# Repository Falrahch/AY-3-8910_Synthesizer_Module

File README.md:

# AY-3-8910_Synthesizer_Module

This respository contains all sources needed to create a synthesizer module based on the AY-3-8910 audio chip from General Instruments. The module is based on a ARM Cortex M3: the STM32F103CBT6.
The module is interfaced by a MIDI controller keyboard over a MIDI interface. The output of the module should be fed into an amplifier and can then be played on a speaker.

## Flashing the Module
The PCB has a SWD interface on the three pins on one side of the microcontroller. The controller can be flashed using and ST-Link V2 flasher and OpenOCD (version 0.10.0-13 should work just fine). The configuration-file in "tools" can be used to do so. The name of the binary has to be changed in the file from "AY-3-8910.bin" to the name of the binary that should be flashed. The binary has to be in the same direction as the config-file (OpenOCD/0.10.0-13/scripts). The flashing process is started via a terminal like powershell:

`openocd -f interface/stlink.cfg -f target/stm32f1x.cfg -f flash_stm32f1x.cfg`

It is possible that the flashing won't work the first time and has to be started a second time.

## Adjusting the Clock Frequency
The clock frequency that is sent to the audio chip can be changed in the source code. This will change the tone range of the chip. With a higher clock frequency the range of playable frequencies will shift up. Also, the resolution between the frequencies will get higher.

Acoording to the manufacturer frequencies between 1 MHz and 2 MHz can be used for the chip. However, up to 8 MHz was tested and works fine without audio distortions.

The frequency for the clock is set in *main.cpp* in the function *setupTimer()*. The register values of Timer 3 have to be set by calculating with the CPU frequncy. Since the CPU frequency is 64 MHz and the clock frequency is set to 2 MHz, the auto-reload value is set to 32. To get different frequencies this register and, if necessary, the prescaler register have to be set. The reference manual and tutorials should be consulted if necessary.

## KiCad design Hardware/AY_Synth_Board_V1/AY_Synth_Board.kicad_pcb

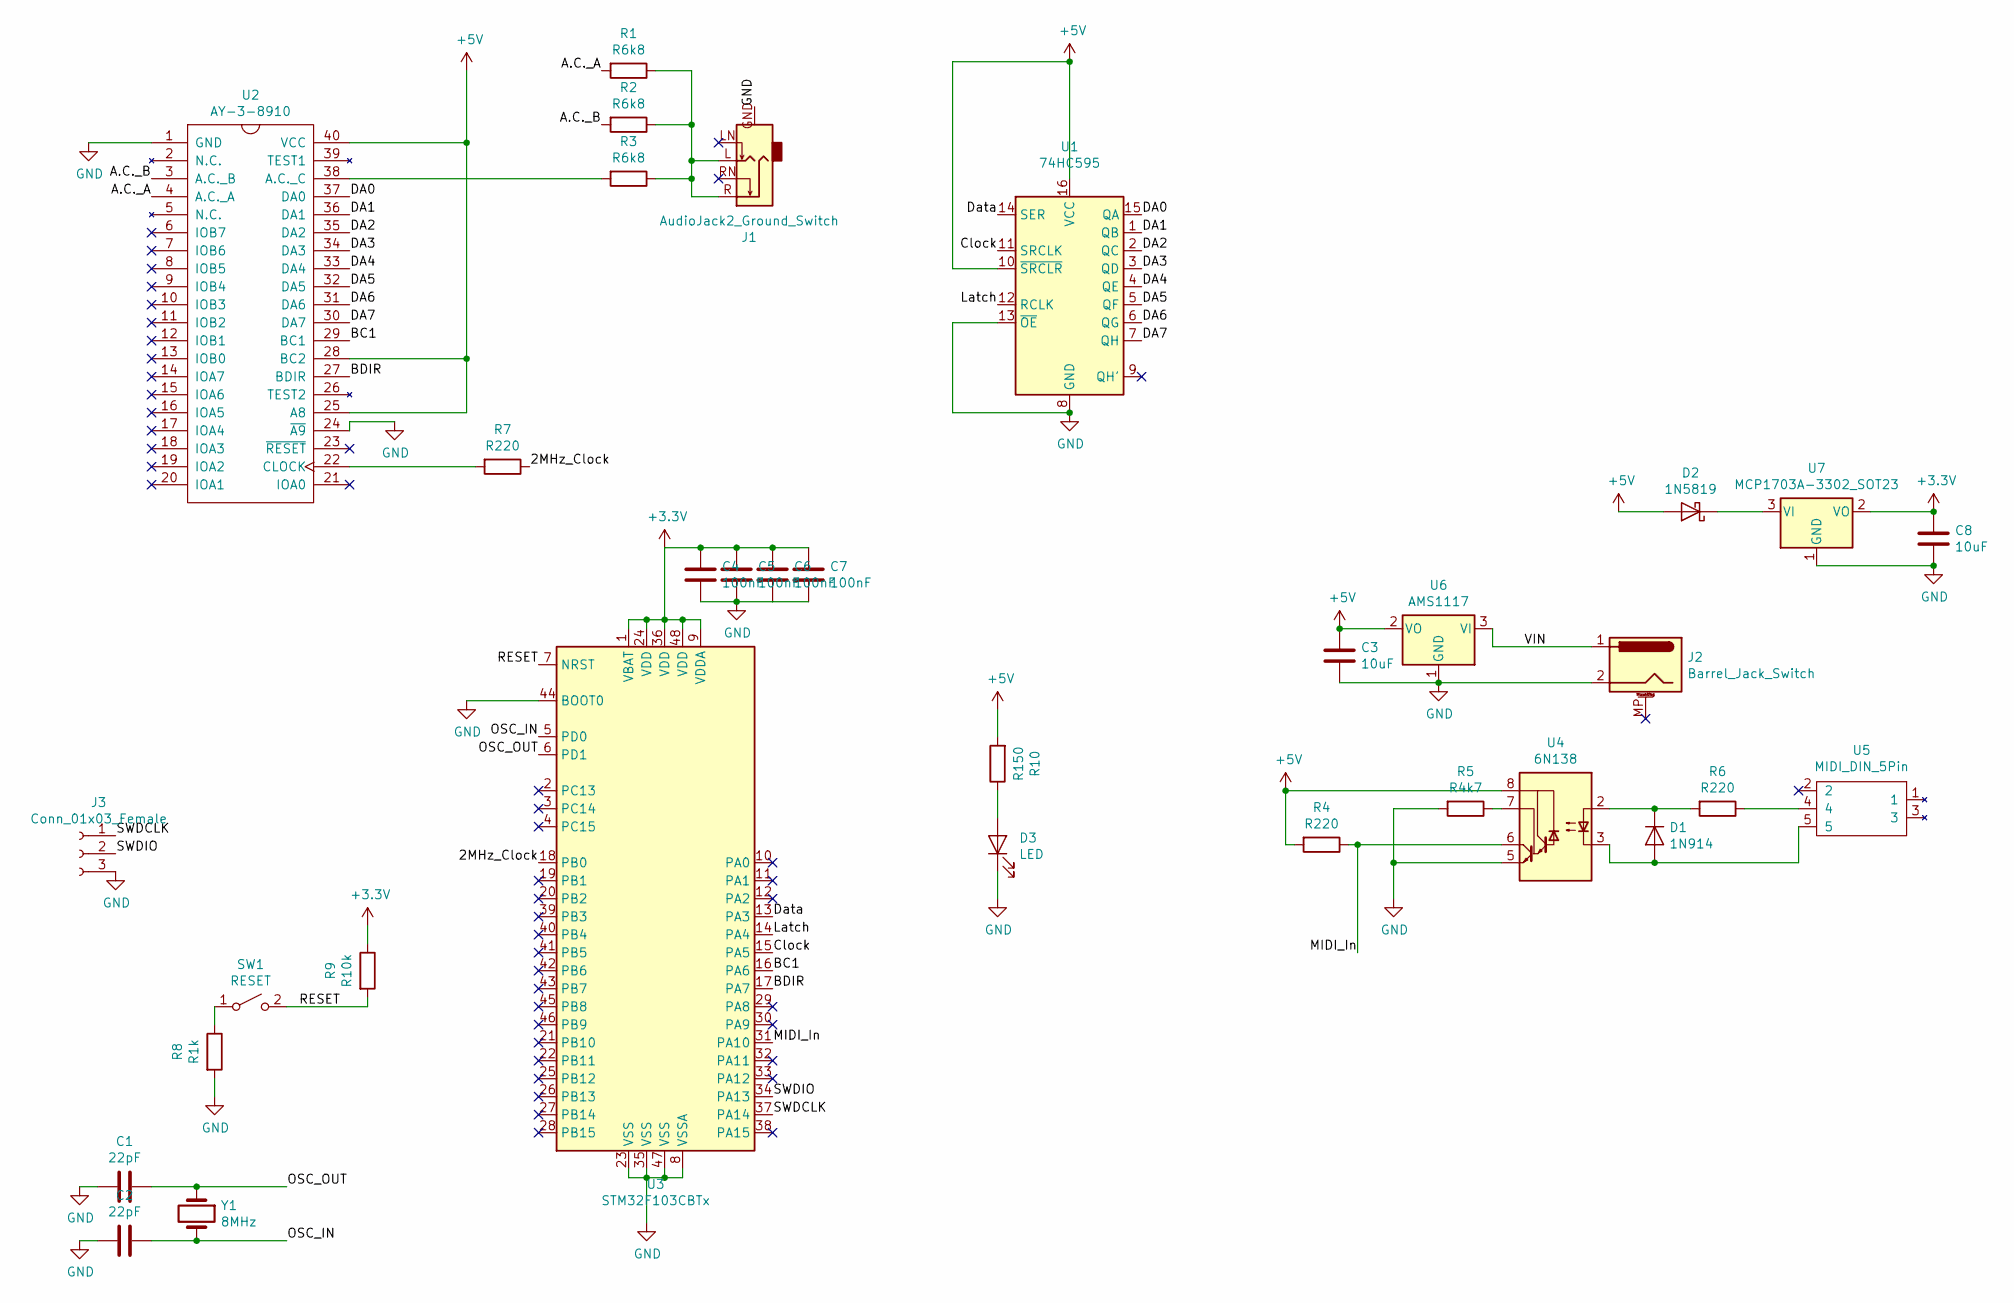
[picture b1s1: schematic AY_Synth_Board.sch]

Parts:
C1, C2: 22pF; C_1206_3216Metric_Pad1.42x1.75mm_HandSolder
C3, C8: 10uF; C_1206_3216Metric_Pad1.42x1.75mm_HandSolder
C4, C5, C6, C7: 100nF; C_1206_3216Metric_Pad1.42x1.75mm_HandSolder
D1: 1N914; D_1206_3216Metric_Pad1.42x1.75mm_HandSolder
D2: 1N5819; D_SOD-123
D3: LED; LED_1206_3216Metric_Pad1.42x1.75mm_HandSolder
J1: AudioJack2_Ground_Switch; Jack_3.5mm_Ledino_KB3SPRS_Horizontal_Custom
J2: Barrel_Jack_Switch; BarrelJack_Horizontal_MP
J3: Conn_01x03_Female; PinHeader_1x03_P2.54mm_Vertical
R1, R2, R3: R6k8; R_1206_3216Metric_Pad1.42x1.75mm_HandSolder
R4, R6, R7: R220; R_1206_3216Metric_Pad1.42x1.75mm_HandSolder
R5: R4k7; R_1206_3216Metric_Pad1.42x1.75mm_HandSolder
R8: R1k; R_1206_3216Metric_Pad1.42x1.75mm_HandSolder
R9: R10k; R_1206_3216Metric_Pad1.42x1.75mm_HandSolder
R10: R150; R_1206_3216Metric_Pad1.42x1.75mm_HandSolder
SW1: RESET; SW_SPST_TL3305A
U1: 74HC595; DIP-16_W7.62mm_Socket
U2: AY-3-8910; DIP-40_W15.24mm_Socket
U3: STM32F103CBTx; LQFP-48_7x7mm_P0.5mm
U4: 6N138; DIP-8_W7.62mm_Socket
U5: MIDI_DIN_5Pin; din_5_econet_pcb_mount
U6: AMS1117; SOT-223
U7: MCP1703A-3302_SOT23; SOT-23
Y1: 8MHz; Crystal_HC18-U_Vertical

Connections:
+3V3: C4.1, C5.1, C6.1, C7.1, C8.1, R9.1, U3.1 (VBAT), U3.9 (VDDA), U3.24 (VDD), U3.36 (VDD), U3.48 (VDD), U7.2 (VO)
+5V: C3.1, D2.2 (A), R4.2, R10.2, U1.10 (~SRCLR), U1.16 (VCC), U2.25 (A8), U2.28 (BC2), U2.40 (VCC), U4.8 (VCC), U6.2 (VO)
/2MHz_Clock: R7.1, U3.18 (PB0)
/A.C._A: R1.2, U2.4 (A.C._A)
/A.C._B: R2.2, U2.3 (A.C._B)
/BC1: U2.29 (BC1), U3.16 (PA6)
/BDIR: U2.27 (BDIR), U3.17 (PA7)
/Clock: U1.11 (SRCLK), U3.15 (PA5)
/DA0: U1.15 (QA), U2.37 (DA0)
/DA1: U1.1 (QB), U2.36 (DA1)
/DA2: U1.2 (QC), U2.35 (DA2)
/DA3: U1.3 (QD), U2.34 (DA3)
/DA4: U1.4 (QE), U2.33 (DA4)
/DA5: U1.5 (QF), U2.32 (DA5)
/DA6: U1.6 (QG), U2.31 (DA6)
/DA7: U1.7 (QH), U2.30 (DA7)
/Data: U1.14 (SER), U3.13 (PA3)
/Latch: U1.12 (RCLK), U3.14 (PA4)
/MIDI_In: R4.1, U3.31 (PA10), U4.6 (VO2)
/OSC_IN: C2.1, U3.5 (PD0), Y1.2
/OSC_OUT: C1.1, U3.6 (PD1), Y1.1
/RESET: R9.2, SW1.2 (B), U3.7 (NRST)
/SWDCLK: J3.1, U3.37 (PA14)
/SWDIO: J3.2, U3.34 (PA13)
/VIN: J2.1, U6.3 (VI)
GND: C1.2, C2.2, C3.2, C4.2, C5.2, C6.2, C7.2, C8.2, D3.1 (K), J1.GND, J2.2, J3.3, R5.2, R8.2, U1.8 (GND), U1.13 (~OE), U2.1 (GND), U2.24 (~A9), U3.8 (VSSA), U3.23 (VSS), U3.35 (VSS), U3.44 (BOOT0), U3.47 (VSS), U4.5 (GND), U6.1 (GND), U7.1 (GND)
unnamed: D1.1 (K), R6.2, U4.2 (C1)
unnamed: D1.2 (A), U4.3 (C2), U5.5
unnamed: D2.1 (K), U7.3 (VI)
unnamed: D3.2 (A), R10.1
unnamed: J1.L, J1.R, R1.1, R2.1, R3.1
unnamed: R3.2, U2.38 (A.C._C)
unnamed: R5.1, U4.7 (VO1)
unnamed: R6.1, U5.4
unnamed: R7.2, U2.22 (CLOCK)
unnamed: R8.1, SW1.1 (A)

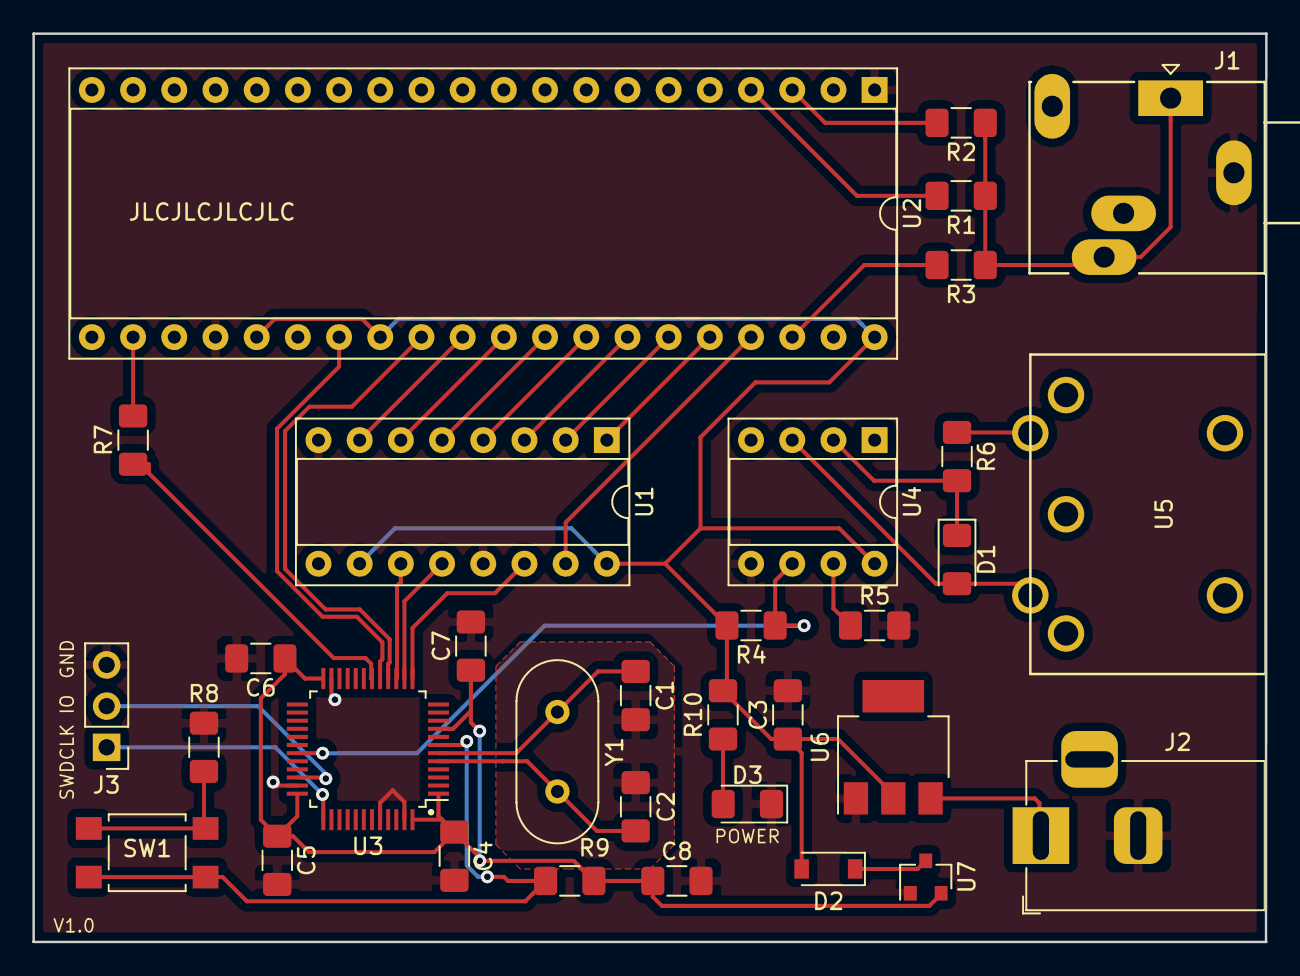
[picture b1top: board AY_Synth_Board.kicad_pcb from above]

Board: 2 copper layers, 76.0 x 56.0 mm, 33 parts (0 on the bottom side), 36 nets.

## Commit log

2020-06-06 Inital commit
2020-06-06 Commit hardware layout files
